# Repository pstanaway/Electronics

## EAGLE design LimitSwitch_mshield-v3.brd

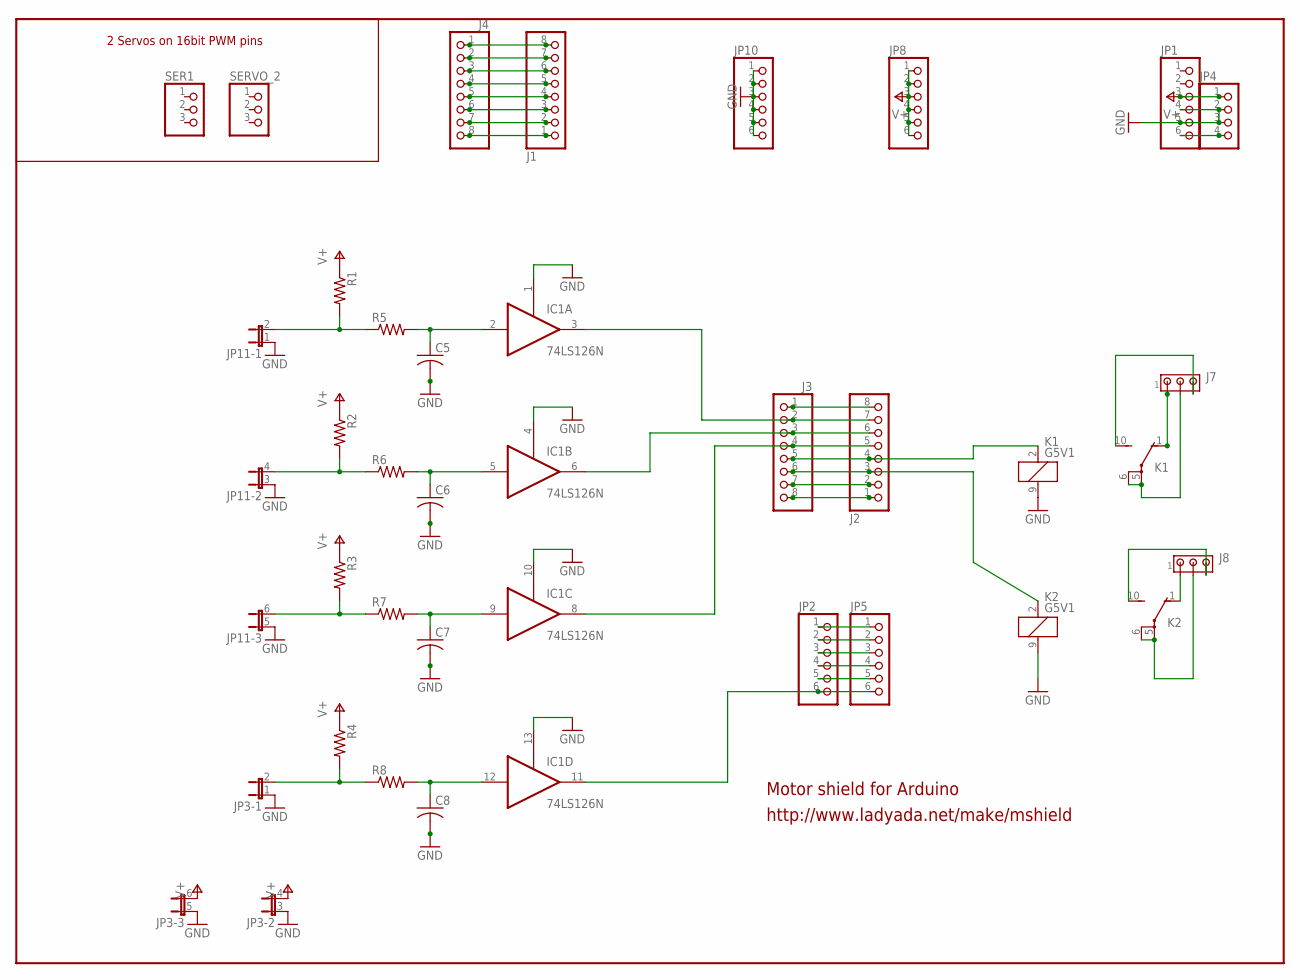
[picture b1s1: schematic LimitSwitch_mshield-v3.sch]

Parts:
C5, C6, C7, C8: C-US025-025X050; C025-025X050
IC1: 74LS126N; DIL14
J1, J2, J3, J4: PINHD-1X8; 1X08
J7, J8: MTA03-100; 10X03MTA
JP1, JP2: PINHD-1X6; 1X06
JP3, JP11: JP3QE; JP3Q
JP4: PINHD-1X4; 1X04
JP5, JP8, JP10: PINHD-1X6B; 1X06-BIG
K1, K2: G5V1
R1, R2, R3, R4, R5, R6, R7, R8: R-US_VMTA55; VMTA55
SER1: PINHD-1X3; 1X03
SERVO_2: PINHD-1X3; 1X03

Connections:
9V: JP1.6, JP4.4
GND: C5.2, C6.2, C7.2, C8.2, IC1.1 (OE), IC1.4 (OE), IC1.7 (GND), IC1.10 (OE), IC1.13 (OE), JP1.4, JP1.5, JP3.1, JP3.3 (1), JP3.5 (1), JP4.2, JP4.3, JP10.1, JP10.2, JP10.3, JP10.4, JP10.5, JP10.6, JP11.1, JP11.3 (1), JP11.5 (1), K1.9 (2), K2.9 (2)
unnamed: J7.2, K1.5, K1.6
unnamed: JP2.1, JP5.1
unnamed: JP2.2, JP5.2
unnamed: JP2.3, JP5.3
unnamed: JP2.4, JP5.4
unnamed: JP2.5, JP5.5
unnamed: J2.8, J3.1
unnamed: IC1.11 (O), JP2.6, JP5.6
unnamed: IC1.6 (O), J2.6, J3.3
unnamed: IC1.8 (O), J2.5, J3.4
unnamed: J2.4, J3.5, K1.2 (1)
unnamed: J2.3, J3.6, K2.2 (1)
unnamed: J8.2, K2.5, K2.6
unnamed: J2.2, J3.7
unnamed: J2.1, J3.8
unnamed: J1.8, J4.1
unnamed: J1.7, J4.2
unnamed: J1.6, J4.3
unnamed: J1.5, J4.4
unnamed: J1.4, J4.5
unnamed: J1.3, J4.6
unnamed: J1.2, J4.7
unnamed: J1.1, J4.8
unnamed: JP11.2, R1.2, R5.1
unnamed: J7.1, K1.1 (O)
unnamed: C6.1, IC1.5 (I), R6.2
unnamed: JP11.4 (2), R2.2, R6.1
unnamed: C7.1, IC1.9 (I), R7.2
unnamed: JP11.6 (2), R3.2, R7.1
unnamed: C8.1, IC1.12 (I), R8.2
unnamed: JP3.2, R4.2, R8.1
unnamed: IC1.3 (O), J2.7, J3.2
unnamed: J7.3, K1.10 (S)
unnamed: J8.1, K2.1 (O)
unnamed: J8.3, K2.10 (S)
unnamed: C5.1, IC1.2 (I), R5.2
V+: JP1.3, JP3.4 (2), JP3.6 (2), JP4.1, JP8.1, JP8.2, JP8.3, JP8.4, JP8.5, JP8.6, R1.1, R2.1, R3.1, R4.1
VCC: IC1.14 (VCC)

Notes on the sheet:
2 Servos on 16bit PWM pins
Motor shield for Arduino
http://www.ladyada.net/make/mshield

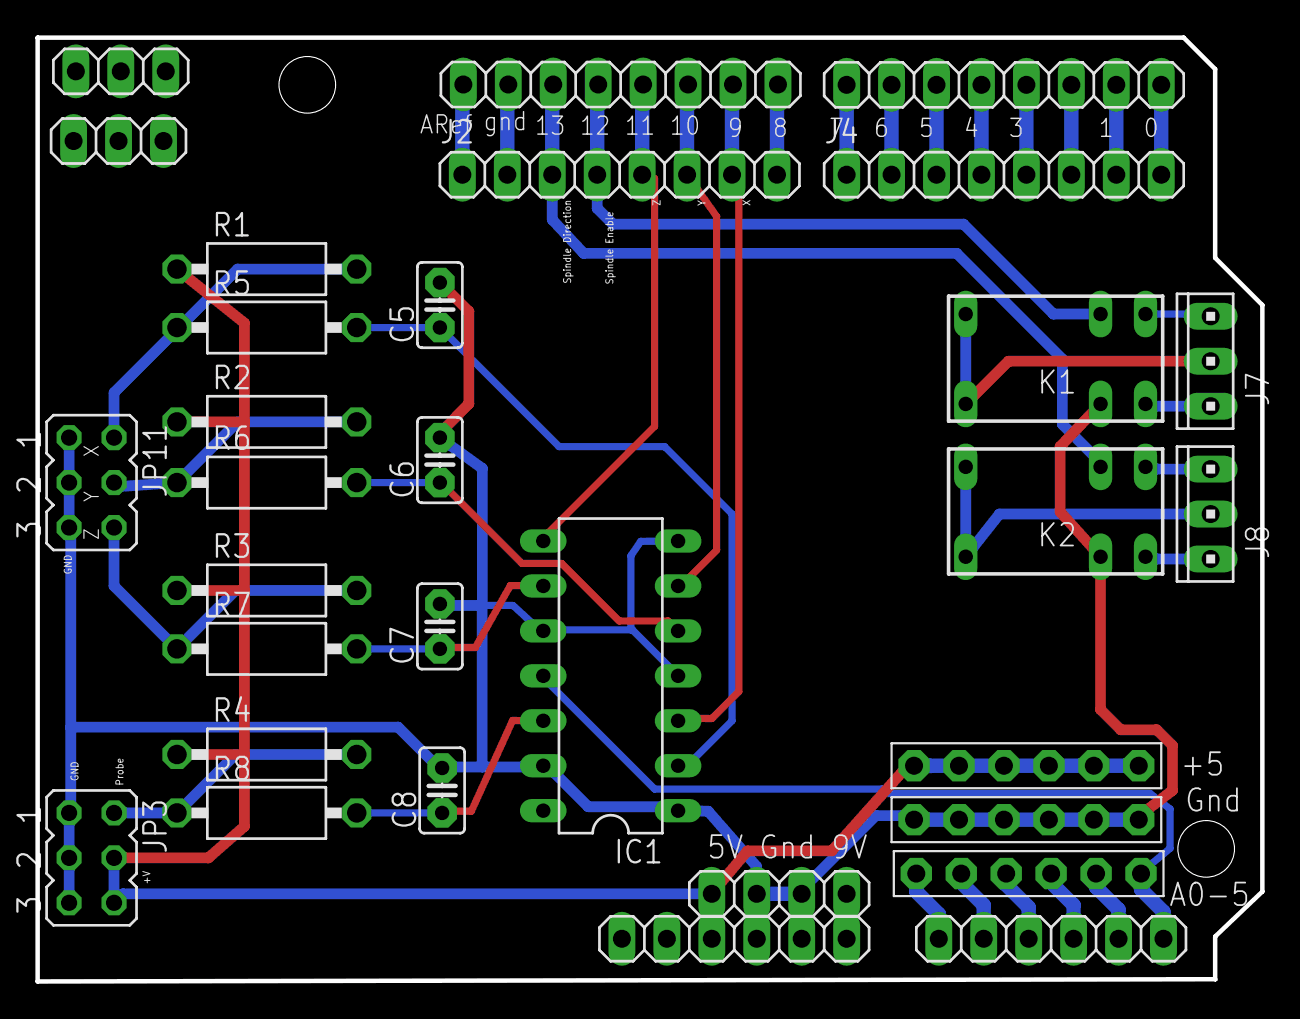
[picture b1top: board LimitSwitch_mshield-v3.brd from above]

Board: 2 copper layers, 69.3 x 53.4 mm, 32 parts (0 on the bottom side), 39 nets.

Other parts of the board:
DRILEGEND: DRILEGEND

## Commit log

2015-01-03 :lollipop: Added .gitattributes & .gitignore files
2015-01-03 Revert ":lollipop: Added .gitattributes & .gitignore files"
    This reverts commit b9a9bc5823e17ebf5107c496db8c070ab7349f03.
2015-01-03 Revert "Revert ":lollipop: Added .gitattributes & .gitignore files""
    This reverts commit 303a3720bc7f6f33467e6f34fc7183fe8f4e80cd.
2015-01-03 Electronic Board for Shapeoko/GRBL shield
2015-01-03 Revert "Electronic Board for Shapeoko/GRBL shield"
    This reverts commit 2fff070545329b35ce621faa40bed2983a9daf5a.
2015-01-03 Revert "Revert "Electronic Board for Shapeoko/GRBL shield""
    This reverts commit ec66accf1123eaf77f7d1930de2c8882c25f6395.
2015-01-03 Revert "Revert "Revert "Electronic Board for Shapeoko/GRBL shield"""
    This reverts commit 40930012659e987f754217c3347009d75741dcff.
2015-01-03 Limit Switch Shield
    A shield for Arduino/GRBL board of the Shapeoko 2 that has a debounce
    circuit(hex schmitt trigger) for the limit switches to remove noise from
    the switches as well as a pair of relays on Spindle control lines that
    can be used to drive other circuits (laser controls).
2015-01-03 Revert "Revert "Revert "Revert "Electronic Board for Shapeoko/GRBL shield""""
    This reverts commit 0fb168dfd44c7e2ee21182399b83e76e1f114d01.
2015-01-03 Revert "Delete LimitSwitch_mshield-v3.sch"
    This reverts commit d8e882cceeb1a9e1a13add4f844dbd2fb25225a7.
